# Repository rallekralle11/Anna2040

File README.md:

# Anna 2040

Similar feature set to the Raspberry pi pico in the classic uno shape.

USB-C

2MB flash memory

all IO pins available

proper analog voltage reference

3,8-32V buck converter with:

lossless reverse polarity protection on the power inputs

data line ESD protection

USB power fuse

LEDs on both pin 13 and 25 as on the uno and pico

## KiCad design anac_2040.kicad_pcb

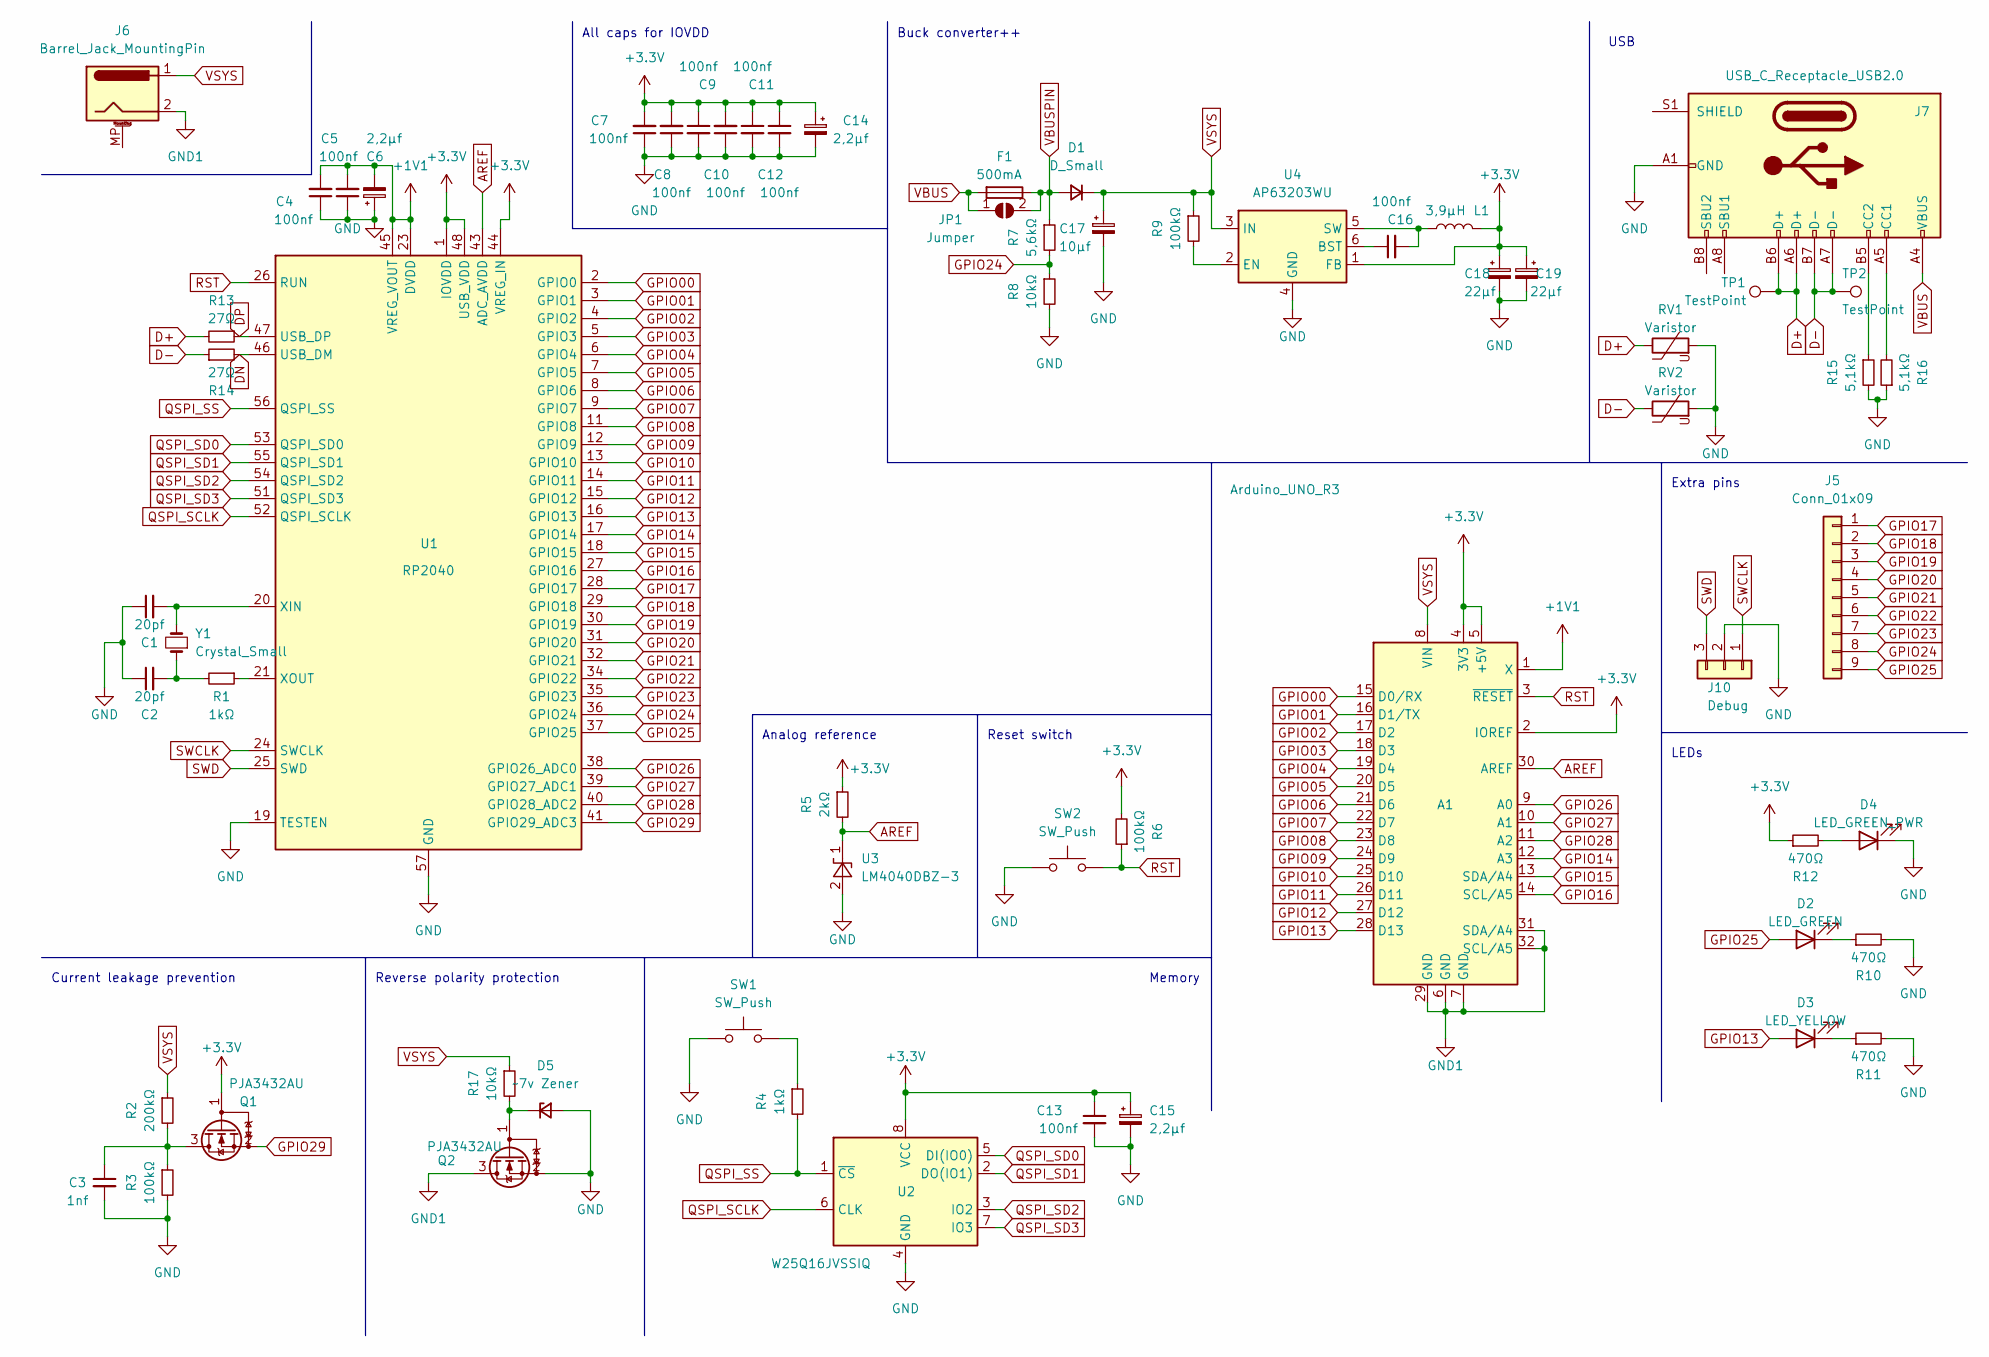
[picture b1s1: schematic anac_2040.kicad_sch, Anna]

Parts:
A1: Arduino_UNO_R3
C1, C2: 20pf; C_0402_1005Metric
C3: 1nf; C_0402_1005Metric
C4, C5, C7, C8, C9, C10, C11, C12, C13, C16: 100nf; C_0402_1005Metric
C6, C14, C15: 2,2µf; C_0402_1005Metric
C17: 10µf; CP_Elec_4x4.5
C18, C19: 22µf; CP_Elec_4x4.5
D1: D_Small; D_SOD-323
D2: LED_GREEN; LED_0402_1005Metric
D3: LED_YELLOW; LED_0402_1005Metric
D4: LED_GREEN_PWR; LED_0402_1005Metric
D5: ~7v Zener; D_SOD-323
F1: 500mA; Fuse_1206_3216Metric
J5: Conn_01x09; PinSocket_1x09_P2.54mm_Vertical
J6: Barrel_Jack_MountingPin; BarrelJack_Horizontal
J7: USB_C_Receptacle_USB2.0; TYPE-C-31-M-12
J10: Debug; PinSocket_1x03_P2.54mm_Vertical
JP1: Jumper; SolderJumper-2_P1.3mm_Open_RoundedPad1.0x1.5mm
L1: 3,9µH; L_Bourns_SRN6045TA
Q1, Q2: PJA3432AU; SOT-23
R1, R4: 1kΩ; R_0402_1005Metric
R2: 200kΩ; R_0402_1005Metric
R3, R6, R9: 100kΩ; R_0402_1005Metric
R5: 2kΩ; R_0402_1005Metric
R7: 5,6kΩ; R_0402_1005Metric
R8, R17: 10kΩ; R_0402_1005Metric
R10, R11, R12: 470Ω; R_0402_1005Metric
R13, R14: 27Ω; R_0402_1005Metric
R15, R16: 5,1kΩ; R_0402_1005Metric
RV1, RV2: Varistor; R_0402_1005Metric
SW1, SW2: SW_Push; SW_Push_1P1T_NO_6x6mm_H9.5mm
TP1, TP2: TestPoint; TestPoint_Pad_D1.5mm
U1: RP2040; QFN-56-1EP_7x7mm_P0.4mm_EP3.2x3.2mm
U2: W25Q16JVSSIQ; SOIC-8_5.23x5.23mm_P1.27mm
U3: LM4040DBZ-3; SOT-23
U4: AP63203WU; TSOT-23-6
Y1: Crystal_Small; Crystal_SMD_7050-2Pin_7.0x5.0mm

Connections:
+1V1: A1.1 (X), C4.2, C5.2, C6.2, U1.23 (DVDD), U1.45 (VREG_VOUT), U1.50 (DVDD)
+3.3V: A1.2 (IOREF), A1.4 (3V3), A1.5 (+5V), C7.2, C8.2, C9.1, C10.2, C11.1, C12.1, C13.1, C14.1, C15.1, C18.1, C19.1, L1.2, Q1.1 (G), R5.1, R6.2, R12.1, U1.1 (IOVDD), U1.10 (IOVDD), U1.22 (IOVDD), U1.33 (IOVDD), U1.42 (IOVDD), U1.44 (VREG_IN), U1.48 (USB_VDD), U1.49 (IOVDD), U2.8 (VCC), U4.1 (FB)
AREF: A1.30 (AREF), R5.2, U1.43 (ADC_AVDD), U3.1 (K)
D+: J7.A6 (D+), J7.B6 (D+), R13.2, RV1.1, TP1.1
D-: J7.A7 (D-), J7.B7 (D-), R14.1, RV2.1, TP2.1
DN: R14.2, U1.46 (USB_DM)
DP: R13.1, U1.47 (USB_DP)
GND: C1.1, C2.1, C3.2, C4.1, C5.1, C6.1, C7.1, C8.1, C9.2, C10.1, C11.2, C12.2, C13.2, C14.2, C15.2, C17.2, C18.2, C19.2, D4.1 (K), D5.2 (A), J7.A1 (GND), J7.A12 (GND), J7.B1 (GND), J7.B12 (GND), J10.2, Q2.2 (S), R3.2, R8.2, R10.2, R11.2, R15.2, R16.1, RV1.2, RV2.2, SW1.1, SW2.1, U1.19 (TESTEN), U1.57 (GND), U2.4 (GND), U3.2 (A), U4.4 (GND)
GND1: A1.6 (GND), A1.7 (GND), A1.29 (GND), A1.31 (SDA/A4), A1.32 (SCL/A5), J6.2, Q2.3 (D)
GPIO00: A1.15 (D0/RX), U1.2 (GPIO0)
GPIO01: A1.16 (D1/TX), U1.3 (GPIO1)
GPIO02: A1.17 (D2), U1.4 (GPIO2)
GPIO03: A1.18 (D3), U1.5 (GPIO3)
GPIO04: A1.19 (D4), U1.6 (GPIO4)
GPIO05: A1.20 (D5), U1.7 (GPIO5)
GPIO06: A1.21 (D6), U1.8 (GPIO6)
GPIO07: A1.22 (D7), U1.9 (GPIO7)
GPIO08: A1.23 (D8), U1.11 (GPIO8)
GPIO09: A1.24 (D9), U1.12 (GPIO9)
GPIO10: A1.25 (D10), U1.13 (GPIO10)
GPIO11: A1.26 (D11), U1.14 (GPIO11)
GPIO12: A1.27 (D12), U1.15 (GPIO12)
GPIO13: A1.28 (D13), D3.2 (A), U1.16 (GPIO13)
GPIO14: A1.12 (A3), U1.17 (GPIO14)
GPIO15: A1.13 (SDA/A4), U1.18 (GPIO15)
GPIO16: A1.14 (SCL/A5), U1.27 (GPIO16)
GPIO17: J5.1, U1.28 (GPIO17)
GPIO18: J5.2, U1.29 (GPIO18)
GPIO19: J5.3, U1.30 (GPIO19)
GPIO20: J5.4, U1.31 (GPIO20)
GPIO21: J5.5, U1.32 (GPIO21)
GPIO22: J5.6, U1.34 (GPIO22)
GPIO23: J5.7, U1.35 (GPIO23)
GPIO24: J5.8, R7.2, R8.1, U1.36 (GPIO24)
GPIO25: D2.2 (A), J5.9, U1.37 (GPIO25)
GPIO26: A1.9 (A0), U1.38 (GPIO26_ADC0)
GPIO27: A1.10 (A1), U1.39 (GPIO27_ADC1)
GPIO28: A1.11 (A2), U1.40 (GPIO28_ADC2)
GPIO29: Q1.2 (S), U1.41 (GPIO29_ADC3)
unnamed: C2.2, R1.2, Y1.1
unnamed: D2.1 (K), R10.1
unnamed: D3.1 (K), R11.1
unnamed: D4.2 (A), R12.2
unnamed: D5.1 (K), Q2.1 (G), R17.2
unnamed: J7.A5 (CC1), R16.2
unnamed: J7.B5 (CC2), R15.1
unnamed: C3.1, Q1.3 (D), R2.2, R3.1
unnamed: R4.1, SW1.2
unnamed: C1.2, U1.20 (XIN), Y1.2
unnamed: R1.1, U1.21 (XOUT)
unnamed: C16.1, U4.6 (BST)
unnamed: R9.2, U4.2 (EN)
unnamed: C16.2, L1.1, U4.5 (SW)
QSPI_SCLK: U1.52 (QSPI_SCLK), U2.6 (CLK)
QSPI_SD0: U1.53 (QSPI_SD0), U2.5 (DI(IO0))
QSPI_SD1: U1.55 (QSPI_SD1), U2.2 (DO(IO1))
QSPI_SD2: U1.54 (QSPI_SD2), U2.3 (IO2)
QSPI_SD3: U1.51 (QSPI_SD3), U2.7 (IO3)
QSPI_SS: R4.2, U1.56 (QSPI_SS), U2.1 (~CS)
RST: A1.3 (~RESET), R6.1, SW2.2, U1.26 (RUN)
SWCLK: J10.1, U1.24 (SWCLK)
SWD: J10.3, U1.25 (SWD)
VBUS: F1.2, J7.A4 (VBUS), J7.A9 (VBUS), J7.B4 (VBUS), J7.B9 (VBUS), JP1.1 (A)
VBUSPIN: D1.2 (A), F1.1, JP1.2 (B), R7.1
VSYS: A1.8 (VIN), C17.1, D1.1 (K), J6.1, R2.1, R9.1, R17.1, U4.3 (IN)

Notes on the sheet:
Memory
Analog reference
Extra pins
Current leakage prevention
All caps for IOVDD
Reverse polarity protection
LEDs
Reset switch
Buck converter++
USB

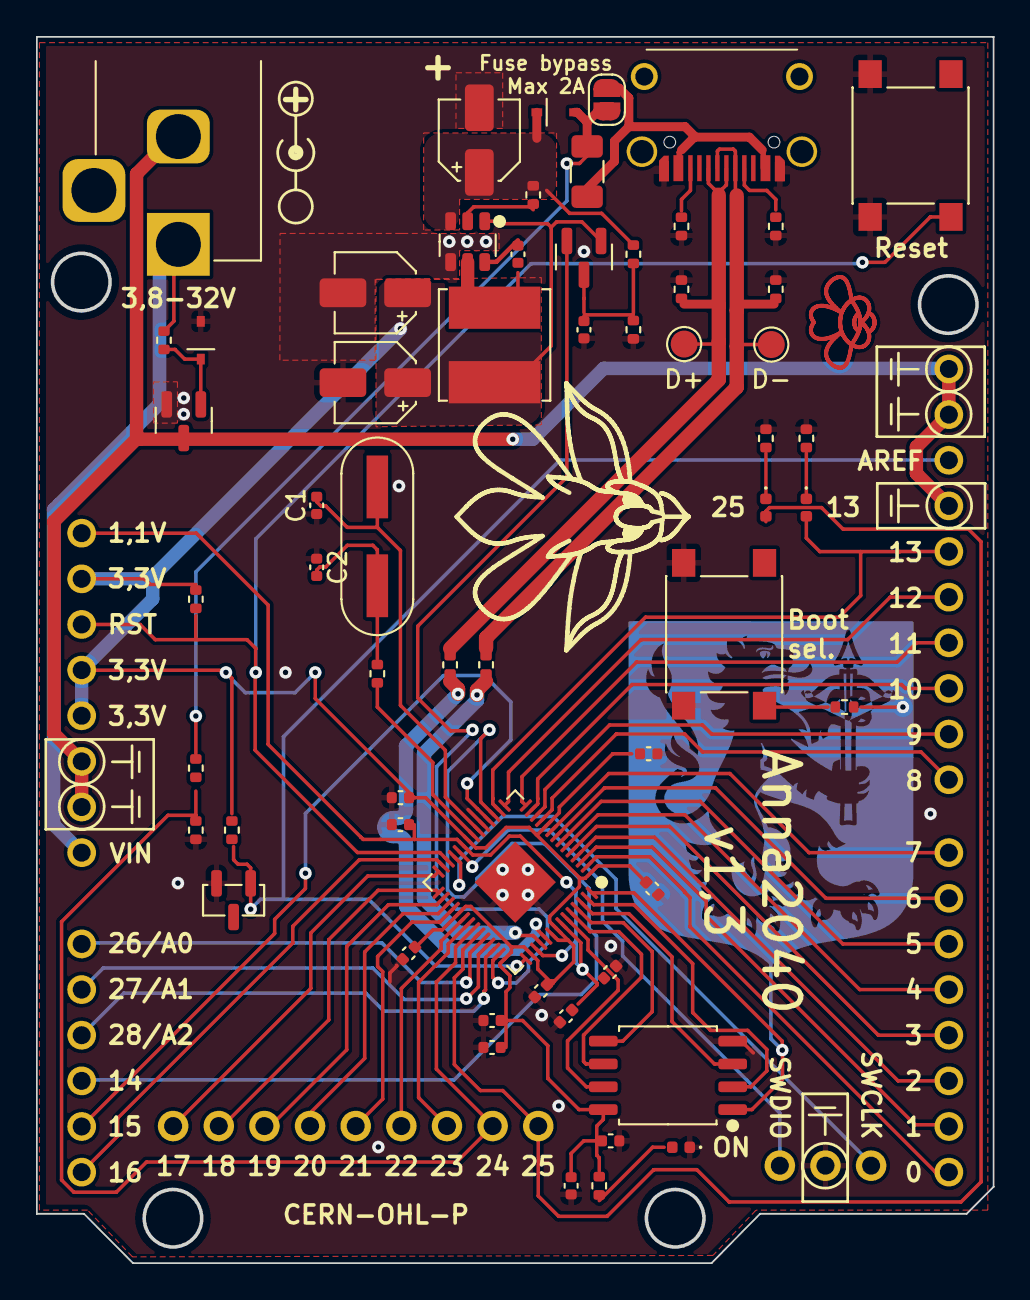
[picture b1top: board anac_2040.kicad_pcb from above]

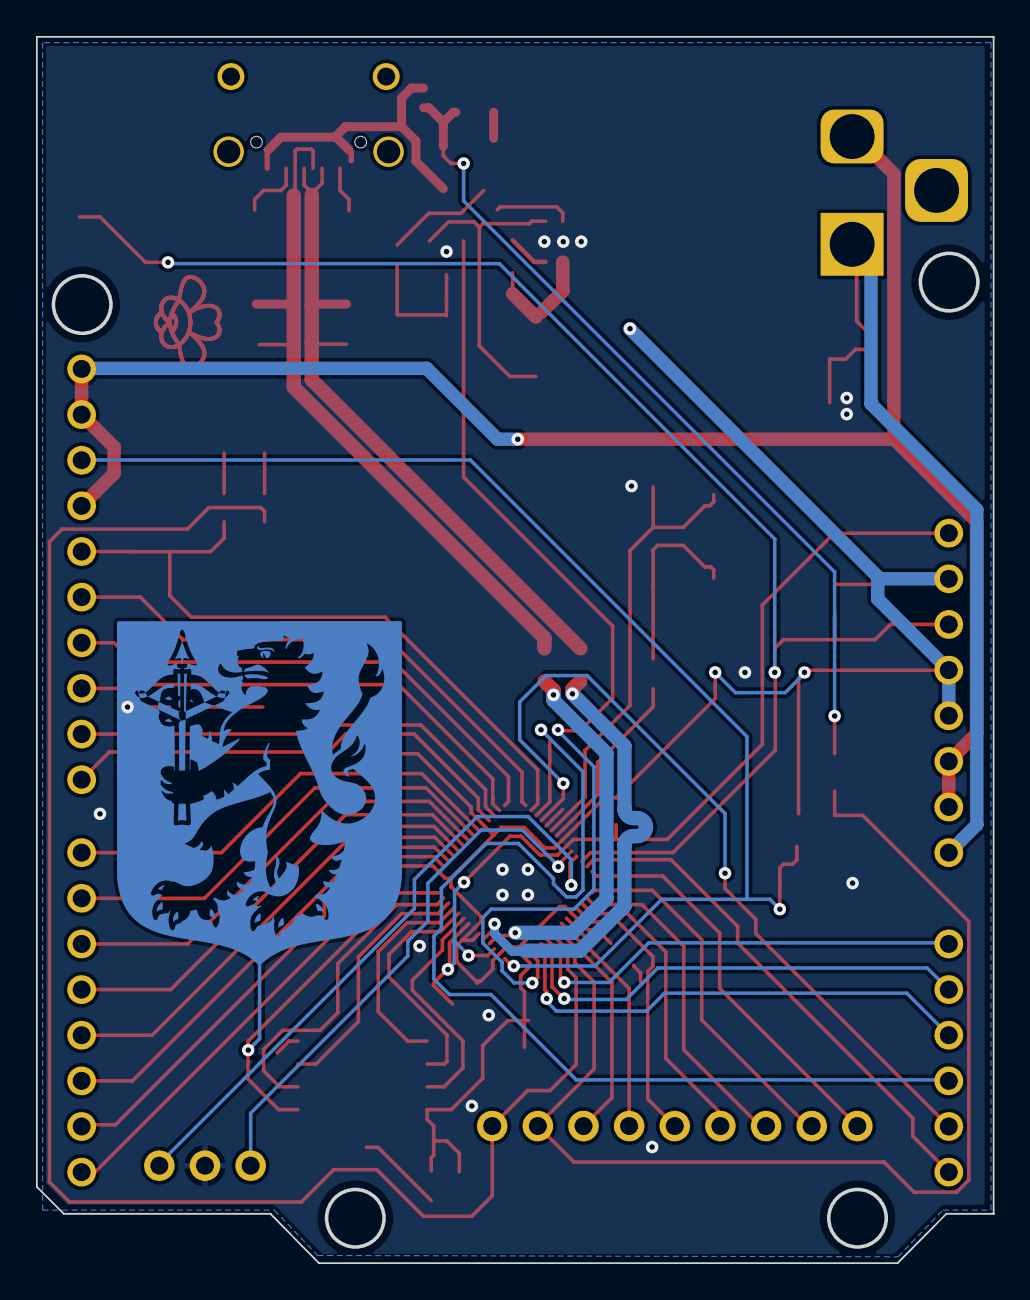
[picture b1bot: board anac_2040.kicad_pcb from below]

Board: 2 copper layers, 53.2 x 68.1 mm, 62 parts (2 on the bottom side), 65 nets.

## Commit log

2022-11-25 initial
2022-11-25 updated picture
2022-11-25 tinkering
2022-11-25 small update
2022-11-25 added gerbers
2022-11-25 fixed things
2022-12-07 few fixes
2022-12-14 i forget
2022-12-17 new BOM and readme update
2022-12-17 small design change
2024-08-14 stuff

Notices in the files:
anac_2040.kicad_pcb:
CERN-OHL-P
